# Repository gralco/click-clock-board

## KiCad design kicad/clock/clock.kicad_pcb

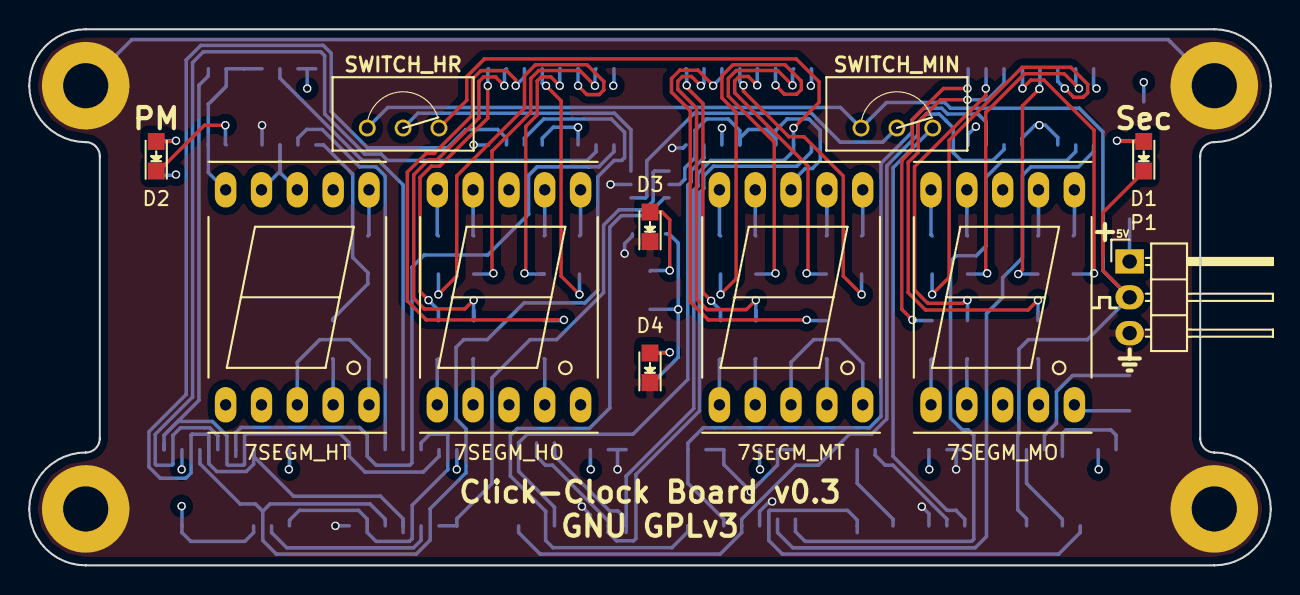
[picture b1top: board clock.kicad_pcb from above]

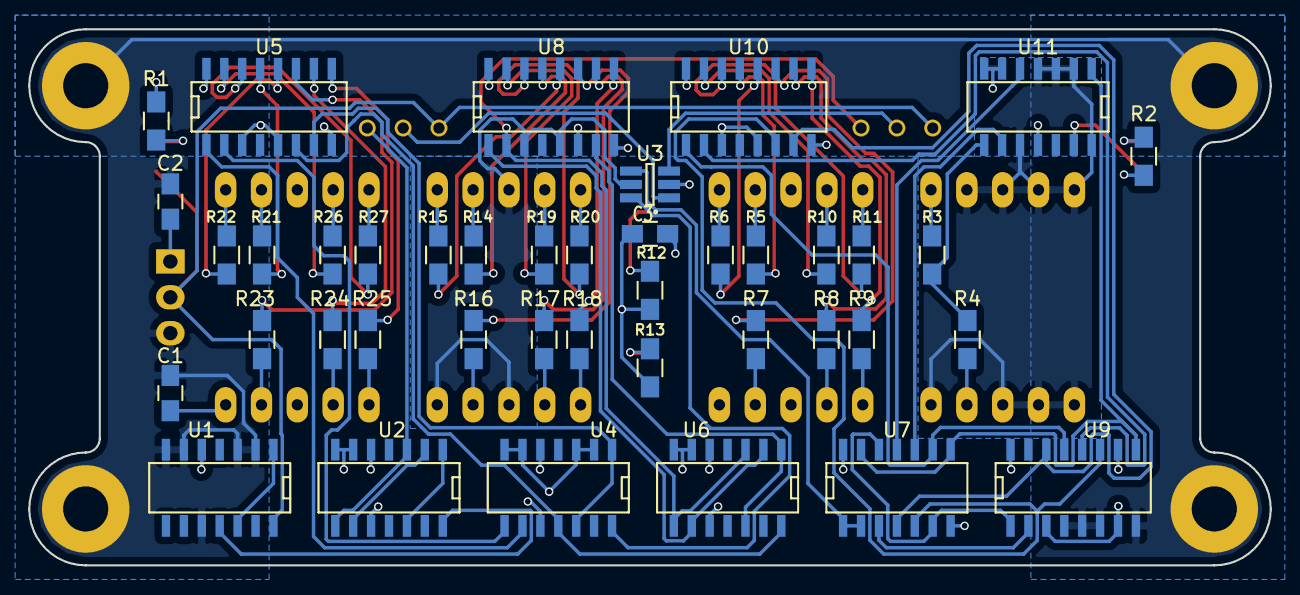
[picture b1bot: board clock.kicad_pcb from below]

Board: 4 copper layers, 88.0 x 38.0 mm, 52 parts (41 on the bottom side), 78 nets.

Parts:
C1, C2: 22μF; C_0805_HandSoldering
C3: 100nF; C_0805_HandSoldering
D1, D2, D3, D4: LED; LED_0805
P1: CONN_01X03; Pin_Header_Angled_1x03
R1, R2, R3, R4, R5, R6, R7, R8, R9, R10, R11, R12, R13, R14, R15, R16, R17, R18, R19, R20, R21, R22, R23, R24, R25, R26, R27: 150Ω; R_0805_HandSoldering
S1: 7SEGM_HT; 7SegmentLED_LTS6760_LTS6780
S2: 7SEGM_HO; 7SegmentLED_LTS6760_LTS6780
S3: 7SEGM_MT; 7SegmentLED_LTS6760_LTS6780
S4: 7SEGM_MO; 7SegmentLED_LTS6760_LTS6780
SW1: SWITCH_MIN; SWITCH_SPDT
SW2: SWITCH_HR; SWITCH_SPDT
U1, U2, U4, U6: 74LS90; SOIC-14
U3: MAX6817; SOT-23-6_Handsoldering
U5, U8, U10: 74LS247; SOIC-16
U7: 74LS00; SOIC-14
U9: 74LS163; SOIC-16
U11: 74LS73; SOIC-14

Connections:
/hoi0: U7.4, U9.14, U10.7
/hoi1: U7.9, U9.13, U10.1
/hoi2: U9.12, U10.2
/hoi3: U7.5, U9.11, U10.6
/hr_one_a: R5.1, U10.13
/hr_one_b: R6.1, U10.12
/hr_one_c: R7.1, U10.11
/hr_one_d: R8.1, U10.10
/hr_one_e: R9.1, U10.9
/hr_one_f: R10.1, U10.15
/hr_one_g: R11.1, U10.14
/ht: R3.1, R4.1, U11.8
/min_one_a: R21.1, U5.13
/min_one_b: R22.1, U5.12
/min_one_c: R23.1, U5.11
/min_one_d: R24.1, U5.10
/min_one_e: R25.1, U5.9
/min_one_f: R26.1, U5.15
/min_one_g: R27.1, U5.14
/min_ten_a: R14.1, U8.13
/min_ten_b: R15.1, U8.12
/min_ten_c: R16.1, U8.11
/min_ten_d: R17.1, U8.10
/min_ten_e: R18.1, U8.9
/min_ten_f: R19.1, U8.15
/min_ten_g: R20.1, U8.14
/moi0: U4.1, U4.12, U5.7
/moi1: U4.9, U5.1
/moi2: U4.8, U5.2
/moi3: U4.11, U5.6, U6.14
/mti0: U6.1, U6.12, U8.7
/mti1: U6.2, U6.9, U8.1
/mti2: SW2.3, U6.3, U6.8, U8.2
/osc: D1.1, P1.2, SW1.1, SW2.1, U1.14
/pm: D2.1, U11.13
GND: C1.2, C2.2, C3.2, D3.1, D4.1, P1.3, U1.2, U1.3, U1.6, U1.7, U1.10, U2.6, U2.7, U2.10, U3.2, U4.2, U4.3, U4.6, U4.7, U4.10, U5.8, U6.6, U6.7, U6.10, U7.7, U8.6, U8.8, U9.4, U9.5, U9.6, U9.8, U10.8, U11.11
unnamed: D1.2, R1.1
unnamed: D2.2, R2.1
unnamed: D3.2, R12.1
unnamed: D4.2, R13.1
unnamed: R3.2, S1.6
unnamed: R4.2, S1.4
unnamed: R5.2, S2.7
unnamed: R6.2, S2.6
unnamed: R7.2, S2.4
unnamed: R8.2, S2.2
unnamed: R9.2, S2.1
unnamed: R10.2, S2.9
unnamed: R11.2, S2.10
unnamed: R14.2, S3.7
unnamed: R15.2, S3.6
unnamed: R16.2, S3.4
unnamed: R17.2, S3.2
unnamed: R18.2, S3.1
unnamed: R19.2, S3.9
unnamed: R20.2, S3.10
unnamed: R21.2, S4.7
unnamed: R22.2, S4.6
unnamed: R23.2, S4.4
unnamed: R24.2, S4.2
unnamed: R25.2, S4.1
unnamed: R26.2, S4.9
unnamed: R27.2, S4.10
unnamed: SW1.2, U3.1
unnamed: SW1.3, U2.3, U2.8
unnamed: SW2.2, U3.3
unnamed: U1.1, U1.12
unnamed: U1.11, U2.14
unnamed: U2.1, U2.12
unnamed: U2.2, U2.9
unnamed: U3.4, U7.1, U7.2
unnamed: U3.6, U4.14
unnamed: U7.3, U9.2
unnamed: U7.6, U7.12, U9.1
unnamed: U7.8, U7.13, U9.9, U11.1
unnamed: U7.11, U11.5
unnamed: U7.10, U11.9
VCC: C1.1, C2.1, C3.1, P1.1, R1.2, R2.2, R12.2, R13.2, S1.1, S1.2, S1.3, S1.5, S1.7, S1.8, S1.9, S1.10, S2.3, S2.5, S2.8, S3.3, S3.5, S3.8, S4.3, S4.5, S4.8, U1.5, U2.5, U3.5, U4.5, U5.3, U5.5, U5.16, U6.5, U7.14, U8.3, U8.5, U8.16, U9.3, U9.7, U9.10, U9.16, U10.3, U10.5, U10.16, U11.2, U11.3, U11.4, U11.6, U11.7, U11.10, U11.14

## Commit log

2017-03-13 Initial commit
    Add all project data
2017-03-13 Add bread board photo
2017-03-19 Continue routing, add two layers
2017-03-19 Add bypass caps and route VCC
2017-03-20 Complete layout, pass DRC, create gerbers
2017-03-20 Add notes to schematic and update pcbnew view
2017-03-20 Add version and license silkscreen text
2017-03-22 Realign components and make the board more symmetric
2017-03-22 Optimize tack and via placement
2017-03-22 Move hr_one_c bottom layer track
2017-03-22 Bring In2.Cu tracks to F.Cu, make In2.Cu pour VCC and F.Cu GND, add pour to the B.Cu left side to GND
2017-03-22 Add more GND pour to the bottom layer
2017-03-22 Update overlapping back pour and set their priority levels
2017-03-22 More routing improvements
2017-03-23 Add BoM, update component info, use 150Ohm current limiting resistors, update layout respectively
2017-03-24 Format the BoM to be more organized, add .ods BoM spreadsheet
2017-03-24 Update 7-seg and sw BoM values
2017-03-24 Update pdf of the schematics
2017-03-24 Add small keep-out zone around pin 8 GND via of U10
2017-03-24 Reduce U9's VCC trace length to pin 3
2017-03-24 Reduce the trace length going to pin 2 of SWITCH_MIN
2017-03-24 Optimize more tracks
2017-03-24 Shorten U1's pin 1 to 12 track
2017-03-24 Use the same routing path for U1, U2, and U4's pin 1 to 12 connection
2017-04-02 Move track going to pin 3 of SW1
2017-04-02 Update netlist after changing resistor values from 220Ohms to 150Ohms
2017-04-03 Close up some copper pour gaps
2017-04-03 Brint input D of U8 to GND
    Was floating
2017-04-03 Swap pin 1 and 3 of the SPDT push button footprint and update layout accordingly
2017-04-03 Make 74163's clk label pos-edge
2017-04-04 Further optimize the routing
2017-04-08 Scooch a few tracks
2017-04-08 Set the mounting hole pitch to be 80mm x 30mm
2017-04-08 Update LED symbol to new KiCad library symbol
2017-04-08 Update switch silkscreen text
2017-04-08 Move R2 such that it's position from the mounting hole on X is the same as R1
2017-04-08 Move R12, R13, and C3's VCC track
2017-04-08 Move U7's pin 8 trace
2017-04-08 Move U11's pin 2 to pin 14 VCC trace
2017-04-08 Expand bottom keepout near U5's GND pin 8
2017-04-08 Clean up tracks and vias
2017-04-08 Center U5, U8, U10, and U11's silkscreen designator
2017-04-08 Reduce min_one_e top layer track length
2017-05-01 Add 5V power supply with oscillator circuit
2017-05-01 Associate more footprints
2017-05-09 Connect the left and right sides of the B.Cu ground pour
    Increment rev to 0.3
    Add title and license to sheet rev block
2017-09-21 Update the C and R WRL 3D model filenames
2017-10-11 Associate some more footprints
2017-10-20 Add new 5V psu and oscillator simulation projects/data, include additional 100uFinput capacitor to the buck converter for less input ripple
2024-01-13 Add Logisim Evolution file

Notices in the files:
kicad/clock/clock.kicad_pcb:
GNU GPLv3
